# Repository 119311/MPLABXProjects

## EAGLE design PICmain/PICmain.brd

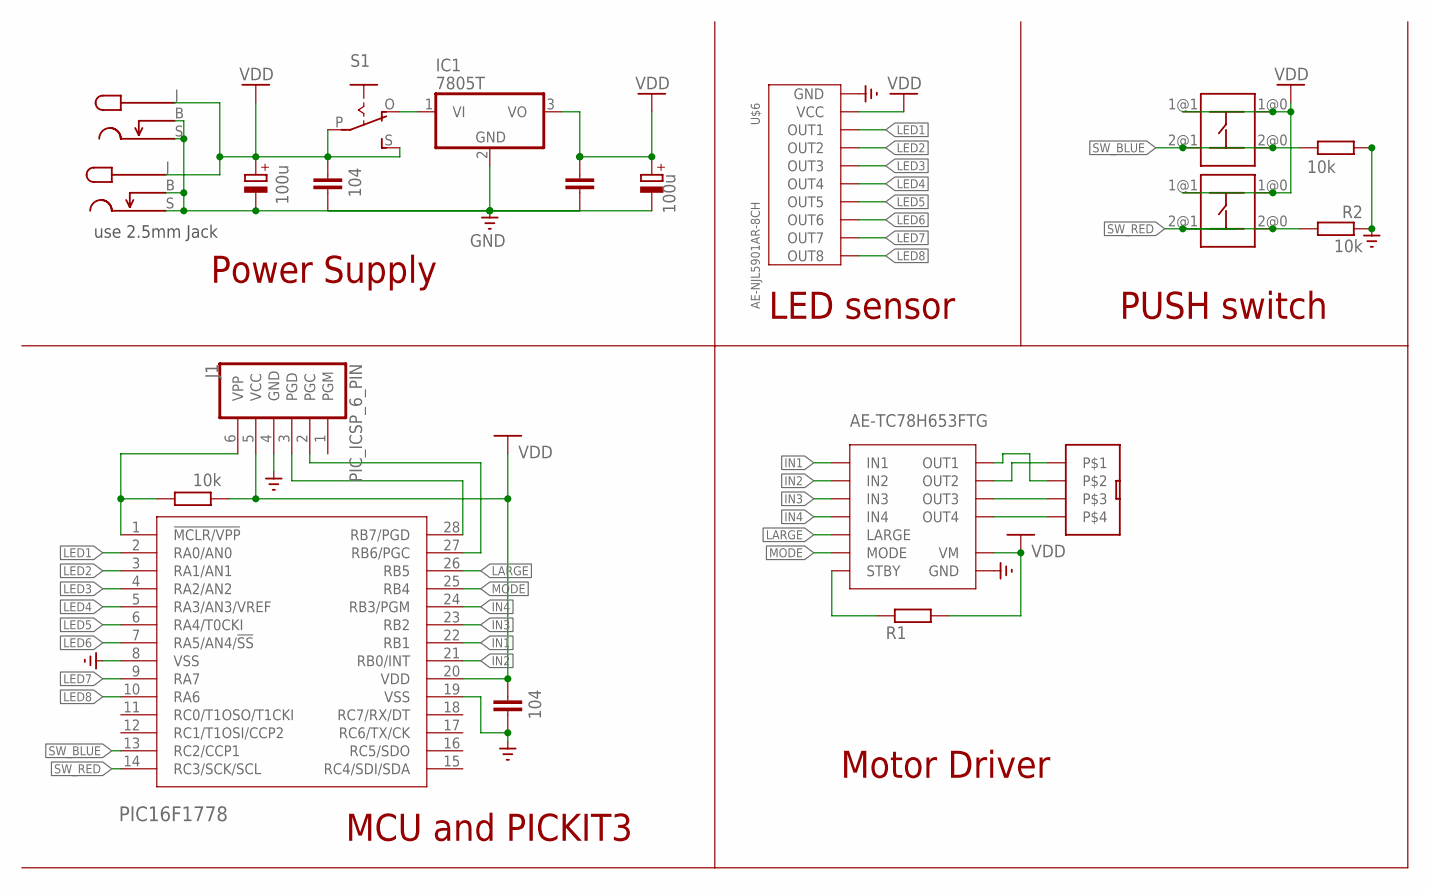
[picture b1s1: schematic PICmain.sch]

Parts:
C1, C4: 100u; E2,5-6
C2, C3, C5: 104; C025-025X050
CONNECTOR1, CONNECTOR2: TACT_SWITCH
IC1: 7805T; TO220H
J1: PIC_ICSP_6_PIN; MOLEX-1X6
R1: R-EU_0204/7; 0204/7
R2, R3, R4: 10k; 0204/7
S1: EG1218S; EG1218
U1: PIC16F1778; DIL28-3
U$1, U$5: MJ-179PH
U$2: 4PIN
U$3: AE-TC78H653FTG
U$6: AE-NJL5901AR-8CH

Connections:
GND: C1.-, C2.2, C3.2, C4.-, C5.2, IC1.2 (GND), J1.4 (GND), R2.1, R4.1, U1.8 (VSS), U1.19 (VSS), U$1.B, U$1.S, U$3.GND@0 (GND), U$3.GND@1 (GND), U$3.GND@2 (GND), U$5.B, U$5.S, U$6.GND
IN1: U1.22 (RB1), U$3.IN1
IN2: U1.21 (RB0/INT), U$3.IN2
IN3: U1.23 (RB2), U$3.IN3
IN4: U1.24 (RB3/PGM), U$3.IN4
LARGE: U1.26 (RB5), U$3.LARGE
LED1: U1.2 (RA0/AN0), U$6.OUT1
LED2: U1.3 (RA1/AN1), U$6.OUT2
LED3: U1.4 (RA2/AN2), U$6.OUT3
LED4: U1.5 (RA3/AN3/VREF), U$6.OUT4
LED5: U1.6 (RA4/T0CKI), U$6.OUT5
LED6: U1.7 (RA5/AN4/!SS), U$6.OUT6
LED7: U1.9 (RA7), U$6.OUT7
LED8: U1.10 (RA6), U$6.OUT8
MDVDD: C1.+, C2.1, R1.2, S1.P, S1.S, U$1.J (L), U$3.VM@0 (VM), U$3.VM@1 (VM), U$5.J (L)
MODE: U1.25 (RB4), U$3.MODE
OUT1: U$2.P$2, U$3.OUT1
OUT2: U$2.P$1, U$3.OUT2
OUT3: U$2.P$3, U$3.OUT3
OUT4: U$2.P$4, U$3.OUT4
PGC: J1.2 (PGC), U1.27 (RB6/PGC)
PGD: J1.3 (PGD), U1.28 (RB7/PGD)
STBY: R1.1, U$3.STBY
SW_BLUE: CONNECTOR1.2@0 (2), CONNECTOR1.2@1 (2), R4.2, U1.13 (RC2/CCP1)
SW_RED: CONNECTOR2.2@0 (2), CONNECTOR2.2@1 (2), R2.2, U1.14 (RC3/SCK/SCL)
VDD: C3.1, C4.+, C5.1, CONNECTOR1.1@0 (1), CONNECTOR1.1@1 (1), CONNECTOR2.1@0 (1), CONNECTOR2.1@1 (1), IC1.3 (VO), J1.5 (VCC), R3.2, U1.20 (VDD), U$6.VIN (VCC)
VI: IC1.1 (VI), S1.O
VPP: J1.6 (VPP), R3.1, U1.1 (!MCLR/VPP)

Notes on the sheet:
use 2.5mm Jack
MCU and PICKIT3
Power Supply
LED sensor
PUSH switch
Motor Driver

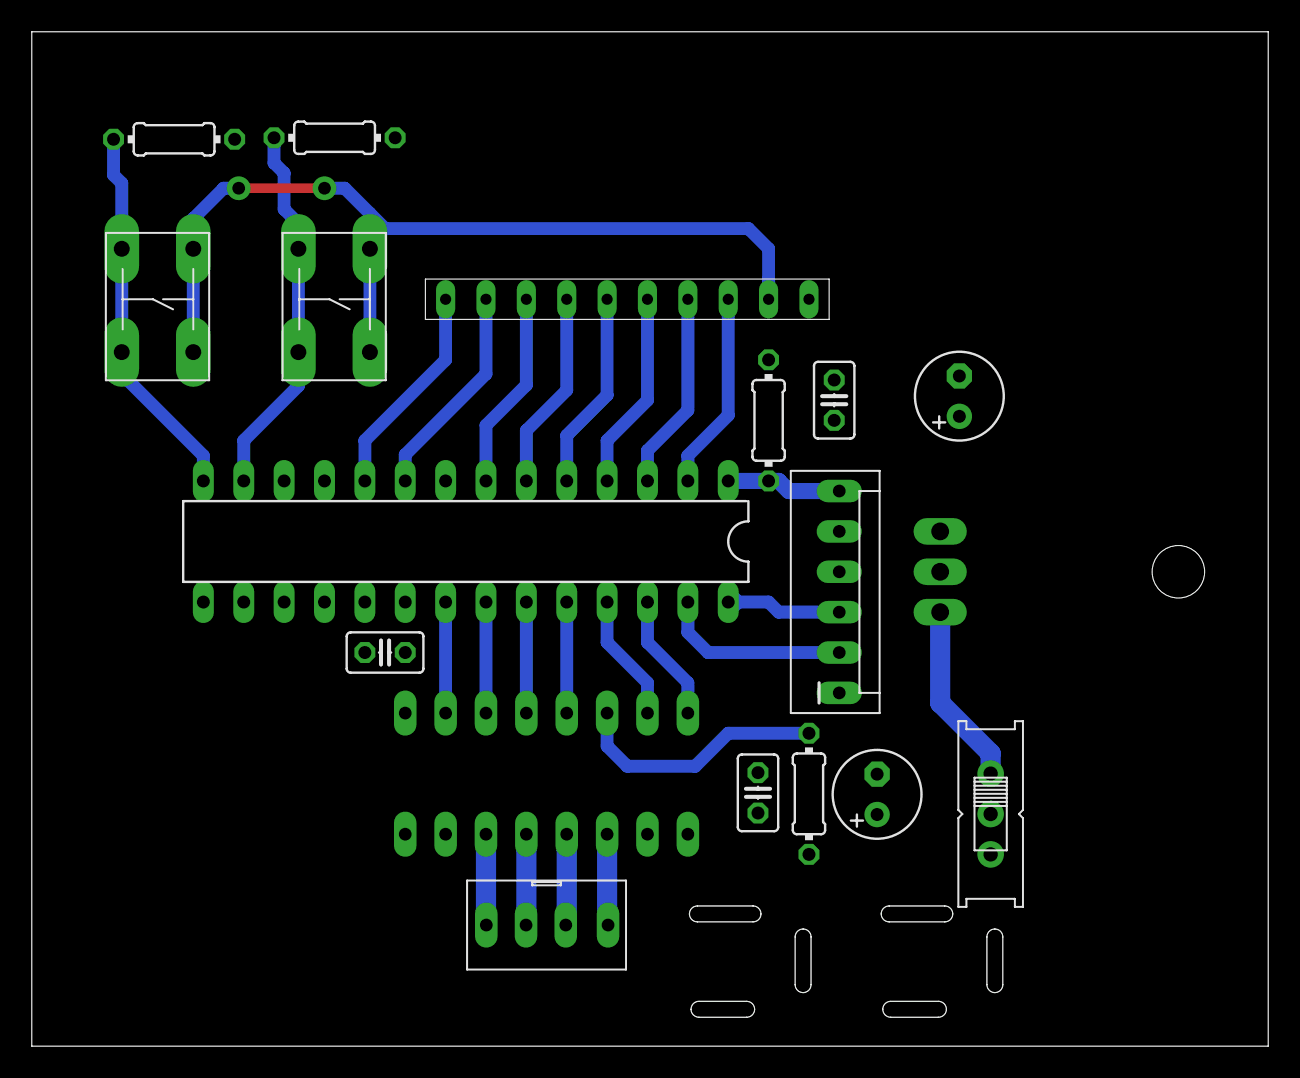
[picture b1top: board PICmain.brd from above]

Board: 2 copper layers, 77.7 x 63.7 mm, 20 parts (1 on the bottom side), 28 nets.

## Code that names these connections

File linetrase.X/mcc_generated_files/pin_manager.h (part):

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// get/set LED1 aliases
#define LED1_TRIS                 TRISAbits.TRISA0
#define LED1_LAT                  LATAbits.LATA0
#define LED1_PORT                 PORTAbits.RA0
#define LED1_WPU                  WPUAbits.WPUA0
#define LED1_OD                   ODCONAbits.ODA0
#define LED1_ANS                  ANSELAbits.ANSA0
#define LED1_SetHigh()            do { LATAbits.LATA0 = 1; } while(0)
#define LED1_SetLow()             do { LATAbits.LATA0 = 0; } while(0)
#define LED1_Toggle()             do { LATAbits.LATA0 = ~LATAbits.LATA0; } while(0)
#define LED1_GetValue()           PORTAbits.RA0
#define LED1_SetDigitalInput()    do { TRISAbits.TRISA0 = 1; } while(0)
#define LED1_SetDigitalOutput()   do { TRISAbits.TRISA0 = 0; } while(0)
#define LED1_SetPullup()          do { WPUAbits.WPUA0 = 1; } while(0)
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// get/set LED2 aliases
#define LED2_TRIS                 TRISAbits.TRISA1
#define LED2_LAT                  LATAbits.LATA1
#define LED2_PORT                 PORTAbits.RA1
#define LED2_WPU                  WPUAbits.WPUA1
#define LED2_OD                   ODCONAbits.ODA1
#define LED2_ANS                  ANSELAbits.ANSA1
#define LED2_SetHigh()            do { LATAbits.LATA1 = 1; } while(0)
#define LED2_SetLow()             do { LATAbits.LATA1 = 0; } while(0)
#define LED2_Toggle()             do { LATAbits.LATA1 = ~LATAbits.LATA1; } while(0)
#define LED2_GetValue()           PORTAbits.RA1
#define LED2_SetDigitalInput()    do { TRISAbits.TRISA1 = 1; } while(0)
#define LED2_SetDigitalOutput()   do { TRISAbits.TRISA1 = 0; } while(0)
#define LED2_SetPullup()          do { WPUAbits.WPUA1 = 1; } while(0)
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// get/set LED3A aliases
#define LED3A_TRIS                 TRISAbits.TRISA2
#define LED3A_LAT                  LATAbits.LATA2
#define LED3A_PORT                 PORTAbits.RA2
#define LED3A_WPU                  WPUAbits.WPUA2
#define LED3A_OD                   ODCONAbits.ODA2
#define LED3A_ANS                  ANSELAbits.ANSA2
#define LED3A_SetHigh()            do { LATAbits.LATA2 = 1; } while(0)
#define LED3A_SetLow()             do { LATAbits.LATA2 = 0; } while(0)
#define LED3A_Toggle()             do { LATAbits.LATA2 = ~LATAbits.LATA2; } while(0)
#define LED3A_GetValue()           PORTAbits.RA2
#define LED3A_SetDigitalInput()    do { TRISAbits.TRISA2 = 1; } while(0)
#define LED3A_SetDigitalOutput()   do { TRISAbits.TRISA2 = 0; } while(0)
#define LED3A_SetPullup()          do { WPUAbits.WPUA2 = 1; } while(0)
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// get/set LED4 aliases
#define LED4_TRIS                 TRISAbits.TRISA3
#define LED4_LAT                  LATAbits.LATA3
#define LED4_PORT                 PORTAbits.RA3
#define LED4_WPU                  WPUAbits.WPUA3
#define LED4_OD                   ODCONAbits.ODA3
#define LED4_ANS                  ANSELAbits.ANSA3
#define LED4_SetHigh()            do { LATAbits.LATA3 = 1; } while(0)
#define LED4_SetLow()             do { LATAbits.LATA3 = 0; } while(0)
#define LED4_Toggle()             do { LATAbits.LATA3 = ~LATAbits.LATA3; } while(0)
#define LED4_GetValue()           PORTAbits.RA3
#define LED4_SetDigitalInput()    do { TRISAbits.TRISA3 = 1; } while(0)
#define LED4_SetDigitalOutput()   do { TRISAbits.TRISA3 = 0; } while(0)
#define LED4_SetPullup()          do { WPUAbits.WPUA3 = 1; } while(0)
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// get/set LED5 aliases
#define LED5_TRIS                 TRISAbits.TRISA4
#define LED5_LAT                  LATAbits.LATA4
#define LED5_PORT                 PORTAbits.RA4
#define LED5_WPU                  WPUAbits.WPUA4
#define LED5_OD                   ODCONAbits.ODA4
#define LED5_ANS                  ANSELAbits.ANSA4
#define LED5_SetHigh()            do { LATAbits.LATA4 = 1; } while(0)
#define LED5_SetLow()             do { LATAbits.LATA4 = 0; } while(0)
#define LED5_Toggle()             do { LATAbits.LATA4 = ~LATAbits.LATA4; } while(0)
#define LED5_GetValue()           PORTAbits.RA4
#define LED5_SetDigitalInput()    do { TRISAbits.TRISA4 = 1; } while(0)
#define LED5_SetDigitalOutput()   do { TRISAbits.TRISA4 = 0; } while(0)
#define LED5_SetPullup()          do { WPUAbits.WPUA4 = 1; } while(0)
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// get/set LED6A aliases
#define LED6A_TRIS                 TRISAbits.TRISA5
#define LED6A_LAT                  LATAbits.LATA5
#define LED6A_PORT                 PORTAbits.RA5
#define LED6A_WPU                  WPUAbits.WPUA5
#define LED6A_OD                   ODCONAbits.ODA5
#define LED6A_ANS                  ANSELAbits.ANSA5
#define LED6A_SetHigh()            do { LATAbits.LATA5 = 1; } while(0)
#define LED6A_SetLow()             do { LATAbits.LATA5 = 0; } while(0)
#define LED6A_Toggle()             do { LATAbits.LATA5 = ~LATAbits.LATA5; } while(0)
#define LED6A_GetValue()           PORTAbits.RA5
#define LED6A_SetDigitalInput()    do { TRISAbits.TRISA5 = 1; } while(0)
#define LED6A_SetDigitalOutput()   do { TRISAbits.TRISA5 = 0; } while(0)
#define LED6A_SetPullup()          do { WPUAbits.WPUA5 = 1; } while(0)
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// get/set LED7 aliases
#define LED7_TRIS                 TRISAbits.TRISA6
#define LED7_LAT                  LATAbits.LATA6
#define LED7_PORT                 PORTAbits.RA6
#define LED7_WPU                  WPUAbits.WPUA6
#define LED7_OD                   ODCONAbits.ODA6
#define LED7_SetHigh()            do { LATAbits.LATA6 = 1; } while(0)
#define LED7_SetLow()             do { LATAbits.LATA6 = 0; } while(0)
#define LED7_Toggle()             do { LATAbits.LATA6 = ~LATAbits.LATA6; } while(0)
#define LED7_GetValue()           PORTAbits.RA6
#define LED7_SetDigitalInput()    do { TRISAbits.TRISA6 = 1; } while(0)
#define LED7_SetDigitalOutput()   do { TRISAbits.TRISA6 = 0; } while(0)
#define LED7_SetPullup()          do { WPUAbits.WPUA6 = 1; } while(0)
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// get/set LED8 aliases
#define LED8_TRIS                 TRISAbits.TRISA7
#define LED8_LAT                  LATAbits.LATA7
#define LED8_PORT                 PORTAbits.RA7
#define LED8_WPU                  WPUAbits.WPUA7
#define LED8_OD                   ODCONAbits.ODA7
#define LED8_SetHigh()            do { LATAbits.LATA7 = 1; } while(0)
#define LED8_SetLow()             do { LATAbits.LATA7 = 0; } while(0)
#define LED8_Toggle()             do { LATAbits.LATA7 = ~LATAbits.LATA7; } while(0)
#define LED8_GetValue()           PORTAbits.RA7
#define LED8_SetDigitalInput()    do { TRISAbits.TRISA7 = 1; } while(0)
#define LED8_SetDigitalOutput()   do { TRISAbits.TRISA7 = 0; } while(0)
#define LED8_SetPullup()          do { WPUAbits.WPUA7 = 1; } while(0)
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// get/set IN2 aliases
#define IN2_TRIS                 TRISBbits.TRISB0
#define IN2_LAT                  LATBbits.LATB0
#define IN2_PORT                 PORTBbits.RB0
#define IN2_WPU                  WPUBbits.WPUB0
#define IN2_ANS                  ANSELBbits.ANSB0
#define IN2_SetHigh()            do { LATBbits.LATB0 = 1; } while(0)
#define IN2_SetLow()             do { LATBbits.LATB0 = 0; } while(0)
#define IN2_Toggle()             do { LATBbits.LATB0 = ~LATBbits.LATB0; } while(0)
#define IN2_GetValue()           PORTBbits.RB0
#define IN2_SetDigitalInput()    do { TRISBbits.TRISB0 = 1; } while(0)
#define IN2_SetDigitalOutput()   do { TRISBbits.TRISB0 = 0; } while(0)
#define IN2_SetPullup()          do { WPUBbits.WPUB0 = 1; } while(0)
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// get/set IN1 aliases
#define IN1_TRIS                 TRISBbits.TRISB1
#define IN1_LAT                  LATBbits.LATB1
#define IN1_PORT                 PORTBbits.RB1
#define IN1_WPU                  WPUBbits.WPUB1
#define IN1_ANS                  ANSELBbits.ANSB1
#define IN1_SetHigh()            do { LATBbits.LATB1 = 1; } while(0)
#define IN1_SetLow()             do { LATBbits.LATB1 = 0; } while(0)
#define IN1_Toggle()             do { LATBbits.LATB1 = ~LATBbits.LATB1; } while(0)
#define IN1_GetValue()           PORTBbits.RB1
#define IN1_SetDigitalInput()    do { TRISBbits.TRISB1 = 1; } while(0)
#define IN1_SetDigitalOutput()   do { TRISBbits.TRISB1 = 0; } while(0)
#define IN1_SetPullup()          do { WPUBbits.WPUB1 = 1; } while(0)
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// get/set IN3 aliases
#define IN3_TRIS                 TRISBbits.TRISB2
#define IN3_LAT                  LATBbits.LATB2
#define IN3_PORT                 PORTBbits.RB2
#define IN3_WPU                  WPUBbits.WPUB2
#define IN3_ANS                  ANSELBbits.ANSB2
#define IN3_SetHigh()            do { LATBbits.LATB2 = 1; } while(0)
#define IN3_SetLow()             do { LATBbits.LATB2 = 0; } while(0)
#define IN3_Toggle()             do { LATBbits.LATB2 = ~LATBbits.LATB2; } while(0)
#define IN3_GetValue()           PORTBbits.RB2
#define IN3_SetDigitalInput()    do { TRISBbits.TRISB2 = 1; } while(0)
#define IN3_SetDigitalOutput()   do { TRISBbits.TRISB2 = 0; } while(0)
#define IN3_SetPullup()          do { WPUBbits.WPUB2 = 1; } while(0)
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// get/set IN4 aliases
#define IN4_TRIS                 TRISBbits.TRISB3
#define IN4_LAT                  LATBbits.LATB3
#define IN4_PORT                 PORTBbits.RB3
#define IN4_WPU                  WPUBbits.WPUB3
#define IN4_ANS                  ANSELBbits.ANSB3
#define IN4_SetHigh()            do { LATBbits.LATB3 = 1; } while(0)
#define IN4_SetLow()             do { LATBbits.LATB3 = 0; } while(0)
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
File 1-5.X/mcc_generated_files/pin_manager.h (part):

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// get/set IO_RA0 aliases
#define IO_RA0_TRIS                 TRISAbits.TRISA0
#define IO_RA0_LAT                  LATAbits.LATA0
#define IO_RA0_PORT                 PORTAbits.RA0
#define IO_RA0_WPU                  WPUAbits.WPUA0
#define IO_RA0_OD                   ODCONAbits.ODA0
#define IO_RA0_ANS                  ANSELAbits.ANSA0
#define IO_RA0_SetHigh()            do { LATAbits.LATA0 = 1; } while(0)
#define IO_RA0_SetLow()             do { LATAbits.LATA0 = 0; } while(0)
#define IO_RA0_Toggle()             do { LATAbits.LATA0 = ~LATAbits.LATA0; } while(0)
#define IO_RA0_GetValue()           PORTAbits.RA0
#define IO_RA0_SetDigitalInput()    do { TRISAbits.TRISA0 = 1; } while(0)
#define IO_RA0_SetDigitalOutput()   do { TRISAbits.TRISA0 = 0; } while(0)
#define IO_RA0_SetPullup()          do { WPUAbits.WPUA0 = 1; } while(0)
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// get/set IO_RA4 aliases
#define IO_RA4_TRIS                 TRISAbits.TRISA4
#define IO_RA4_LAT                  LATAbits.LATA4
#define IO_RA4_PORT                 PORTAbits.RA4
#define IO_RA4_WPU                  WPUAbits.WPUA4
#define IO_RA4_OD                   ODCONAbits.ODA4
#define IO_RA4_ANS                  ANSELAbits.ANSA4
#define IO_RA4_SetHigh()            do { LATAbits.LATA4 = 1; } while(0)
#define IO_RA4_SetLow()             do { LATAbits.LATA4 = 0; } while(0)
#define IO_RA4_Toggle()             do { LATAbits.LATA4 = ~LATAbits.LATA4; } while(0)
#define IO_RA4_GetValue()           PORTAbits.RA4
#define IO_RA4_SetDigitalInput()    do { TRISAbits.TRISA4 = 1; } while(0)
#define IO_RA4_SetDigitalOutput()   do { TRISAbits.TRISA4 = 0; } while(0)
#define IO_RA4_SetPullup()          do { WPUAbits.WPUA4 = 1; } while(0)
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// get/set IO_RB0 aliases
#define IO_RB0_TRIS                 TRISBbits.TRISB0
#define IO_RB0_LAT                  LATBbits.LATB0
#define IO_RB0_PORT                 PORTBbits.RB0
#define IO_RB0_WPU                  WPUBbits.WPUB0
#define IO_RB0_ANS                  ANSELBbits.ANSB0
#define IO_RB0_SetHigh()            do { LATBbits.LATB0 = 1; } while(0)
#define IO_RB0_SetLow()             do { LATBbits.LATB0 = 0; } while(0)
#define IO_RB0_Toggle()             do { LATBbits.LATB0 = ~LATBbits.LATB0; } while(0)
#define IO_RB0_GetValue()           PORTBbits.RB0
#define IO_RB0_SetDigitalInput()    do { TRISBbits.TRISB0 = 1; } while(0)
#define IO_RB0_SetDigitalOutput()   do { TRISBbits.TRISB0 = 0; } while(0)
#define IO_RB0_SetPullup()          do { WPUBbits.WPUB0 = 1; } while(0)
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// get/set IO_RB1 aliases
#define IO_RB1_TRIS                 TRISBbits.TRISB1
#define IO_RB1_LAT                  LATBbits.LATB1
#define IO_RB1_PORT                 PORTBbits.RB1
#define IO_RB1_WPU                  WPUBbits.WPUB1
#define IO_RB1_ANS                  ANSELBbits.ANSB1
#define IO_RB1_SetHigh()            do { LATBbits.LATB1 = 1; } while(0)
#define IO_RB1_SetLow()             do { LATBbits.LATB1 = 0; } while(0)
#define IO_RB1_Toggle()             do { LATBbits.LATB1 = ~LATBbits.LATB1; } while(0)
#define IO_RB1_GetValue()           PORTBbits.RB1
#define IO_RB1_SetDigitalInput()    do { TRISBbits.TRISB1 = 1; } while(0)
#define IO_RB1_SetDigitalOutput()   do { TRISBbits.TRISB1 = 0; } while(0)
#define IO_RB1_SetPullup()          do { WPUBbits.WPUB1 = 1; } while(0)
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// get/set IO_RB2 aliases
#define IO_RB2_TRIS                 TRISBbits.TRISB2
#define IO_RB2_LAT                  LATBbits.LATB2
#define IO_RB2_PORT                 PORTBbits.RB2
#define IO_RB2_WPU                  WPUBbits.WPUB2
#define IO_RB2_ANS                  ANSELBbits.ANSB2
#define IO_RB2_SetHigh()            do { LATBbits.LATB2 = 1; } while(0)
#define IO_RB2_SetLow()             do { LATBbits.LATB2 = 0; } while(0)
#define IO_RB2_Toggle()             do { LATBbits.LATB2 = ~LATBbits.LATB2; } while(0)
#define IO_RB2_GetValue()           PORTBbits.RB2
#define IO_RB2_SetDigitalInput()    do { TRISBbits.TRISB2 = 1; } while(0)
#define IO_RB2_SetDigitalOutput()   do { TRISBbits.TRISB2 = 0; } while(0)
#define IO_RB2_SetPullup()          do { WPUBbits.WPUB2 = 1; } while(0)
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// get/set IO_RB3 aliases
#define IO_RB3_TRIS                 TRISBbits.TRISB3
#define IO_RB3_LAT                  LATBbits.LATB3
#define IO_RB3_PORT                 PORTBbits.RB3
#define IO_RB3_WPU                  WPUBbits.WPUB3
#define IO_RB3_ANS                  ANSELBbits.ANSB3
#define IO_RB3_SetHigh()            do { LATBbits.LATB3 = 1; } while(0)
#define IO_RB3_SetLow()             do { LATBbits.LATB3 = 0; } while(0)
#define IO_RB3_Toggle()             do { LATBbits.LATB3 = ~LATBbits.LATB3; } while(0)
#define IO_RB3_GetValue()           PORTBbits.RB3
#define IO_RB3_SetDigitalInput()    do { TRISBbits.TRISB3 = 1; } while(0)
#define IO_RB3_SetDigitalOutput()   do { TRISBbits.TRISB3 = 0; } while(0)
#define IO_RB3_SetPullup()          do { WPUBbits.WPUB3 = 1; } while(0)
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// get/set IO_RB4 aliases
#define IO_RB4_TRIS                 TRISBbits.TRISB4
#define IO_RB4_LAT                  LATBbits.LATB4
#define IO_RB4_PORT                 PORTBbits.RB4
#define IO_RB4_WPU                  WPUBbits.WPUB4
#define IO_RB4_OD                   ODCONBbits.ODB4
#define IO_RB4_ANS                  ANSELBbits.ANSB4
#define IO_RB4_SetHigh()            do { LATBbits.LATB4 = 1; } while(0)
#define IO_RB4_SetLow()             do { LATBbits.LATB4 = 0; } while(0)
#define IO_RB4_Toggle()             do { LATBbits.LATB4 = ~LATBbits.LATB4; } while(0)
#define IO_RB4_GetValue()           PORTBbits.RB4
#define IO_RB4_SetDigitalInput()    do { TRISBbits.TRISB4 = 1; } while(0)
#define IO_RB4_SetDigitalOutput()   do { TRISBbits.TRISB4 = 0; } while(0)
#define IO_RB4_SetPullup()          do { WPUBbits.WPUB4 = 1; } while(0)
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// get/set IO_RB5 aliases
#define IO_RB5_TRIS                 TRISBbits.TRISB5
#define IO_RB5_LAT                  LATBbits.LATB5
#define IO_RB5_PORT                 PORTBbits.RB5
#define IO_RB5_WPU                  WPUBbits.WPUB5
#define IO_RB5_OD                   ODCONBbits.ODB5
#define IO_RB5_ANS                  ANSELBbits.ANSB5
#define IO_RB5_SetHigh()            do { LATBbits.LATB5 = 1; } while(0)
#define IO_RB5_SetLow()             do { LATBbits.LATB5 = 0; } while(0)
#define IO_RB5_Toggle()             do { LATBbits.LATB5 = ~LATBbits.LATB5; } while(0)
#define IO_RB5_GetValue()           PORTBbits.RB5
#define IO_RB5_SetDigitalInput()    do { TRISBbits.TRISB5 = 1; } while(0)
#define IO_RB5_SetDigitalOutput()   do { TRISBbits.TRISB5 = 0; } while(0)
#define IO_RB5_SetPullup()          do { WPUBbits.WPUB5 = 1; } while(0)
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// get/set IO_RB6 aliases
#define IO_RB6_TRIS                 TRISBbits.TRISB6
#define IO_RB6_LAT                  LATBbits.LATB6
#define IO_RB6_PORT                 PORTBbits.RB6
#define IO_RB6_WPU                  WPUBbits.WPUB6
#define IO_RB6_OD                   ODCONBbits.ODB6
#define IO_RB6_SetHigh()            do { LATBbits.LATB6 = 1; } while(0)
#define IO_RB6_SetLow()             do { LATBbits.LATB6 = 0; } while(0)
#define IO_RB6_Toggle()             do { LATBbits.LATB6 = ~LATBbits.LATB6; } while(0)
#define IO_RB6_GetValue()           PORTBbits.RB6
#define IO_RB6_SetDigitalInput()    do { TRISBbits.TRISB6 = 1; } while(0)
#define IO_RB6_SetDigitalOutput()   do { TRISBbits.TRISB6 = 0; } while(0)
#define IO_RB6_SetPullup()          do { WPUBbits.WPUB6 = 1; } while(0)
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// get/set IO_RB7 aliases
#define IO_RB7_TRIS                 TRISBbits.TRISB7
#define IO_RB7_LAT                  LATBbits.LATB7
#define IO_RB7_PORT                 PORTBbits.RB7
#define IO_RB7_WPU                  WPUBbits.WPUB7
#define IO_RB7_OD                   ODCONBbits.ODB7
#define IO_RB7_SetHigh()            do { LATBbits.LATB7 = 1; } while(0)
#define IO_RB7_SetLow()             do { LATBbits.LATB7 = 0; } while(0)
#define IO_RB7_Toggle()             do { LATBbits.LATB7 = ~LATBbits.LATB7; } while(0)
#define IO_RB7_GetValue()           PORTBbits.RB7
#define IO_RB7_SetDigitalInput()    do { TRISBbits.TRISB7 = 1; } while(0)
#define IO_RB7_SetDigitalOutput()   do { TRISBbits.TRISB7 = 0; } while(0)
#define IO_RB7_SetPullup()          do { WPUBbits.WPUB7 = 1; } while(0)
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
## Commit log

2022-05-24 init
2022-05-24 5-24
2022-05-25 end 1
2022-05-28 update main
2022-05-28 add 1
2022-05-28 add 2
2022-05-28 add macro
2022-05-28 good by
2022-05-28 add interrupt (need to mcc)
2022-05-28 add MOTOR WRITE (no implementation )
2022-05-28 update interrupt
2022-05-28 update pwm
2022-05-28 fix typo
2022-05-28 update 3
2022-05-31 結果にコミットする男
2022-06-23 refactor: :art: format
2022-06-23 feat: :bento: report
    add md
2022-09-12 format
2022-09-12 add 3-1
2022-09-12 add linetrase
2022-09-12 add linetraser
2022-09-13 aaaaa
2022-09-13 add module
2022-09-13 update mcc
2022-09-13 add motor
2022-09-13 marge onedrive
2022-09-16 move led
2022-09-18 update motor
2022-09-19 MAKE SRC
2022-09-20 move main
2022-09-20 update member
2022-09-20 update member of motor
2022-09-20 I got moved
2022-09-21 format and delete debug
2022-09-21 powerrrrrrrrrr
2022-09-21 add autopilot
2022-09-22 update LED
2022-09-22 temp commit
2022-09-22 update aP
2022-09-23 test pid
2022-09-27 temp
2022-09-29 run forward
2022-10-09 end report
2022-10-21 base

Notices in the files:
1-5.X/mcc_generated_files/pin_manager.h:
(c) 2018 Microchip Technology Inc. and its subsidiaries.
parts and their libraries:
SparkFun-Connectors: Licensing: Creative Commons ShareAlike 4.0 International - https://creativecommons.org/licenses/by-sa/4.0
supply0: Copyright (C) 2007, Bob Starr
